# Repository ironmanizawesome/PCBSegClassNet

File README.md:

# PCB 회로도 복원 (Monorepo)

PCB 기판 사진으로부터 회로도(netlist)를 복원하는 프로젝트.
전체 목표·트랙 구조는 [project_outline.md](project_outline.md) 참조.

## 구조

```
.
├── component_seg/    Track B 1단계: 부품 검출/세그멘테이션 (TF, PCBSegClassNet 기반)
├── trace_seg/        Track B 3단계: 배선(trace) 세그멘테이션 (PyTorch, 자체 개발)
├── project_outline.md  프로젝트 전체 outline (Track A/B/C)
└── README.md
```

각 sub-project는 자체적인 `README.md`, `CLAUDE.md`, `requirements.txt`를
가짐. 두 프로젝트는 의존성·기술 스택이 분리됨 (TF vs PyTorch) — 한쪽에서
작업할 때는 해당 폴더로 `cd` 후 진행.

## 빠른 시작

```bash
# 부품 검출 작업
cd component_seg
# (component_seg/README.md 참조)

# 배선 검출 작업
cd trace_seg
# (trace_seg/README.md 참조)
```

## History

- `component_seg/`: 원래 [CandleLabAI/PCBSegClassNet](https://github.com/CandleLabAI/PCBSegClassNet) fork에서 출발, Arduino transfer learning 작업 추가
- `trace_seg/`: 자체 개발 (subtree merge로 통합, history 보존)

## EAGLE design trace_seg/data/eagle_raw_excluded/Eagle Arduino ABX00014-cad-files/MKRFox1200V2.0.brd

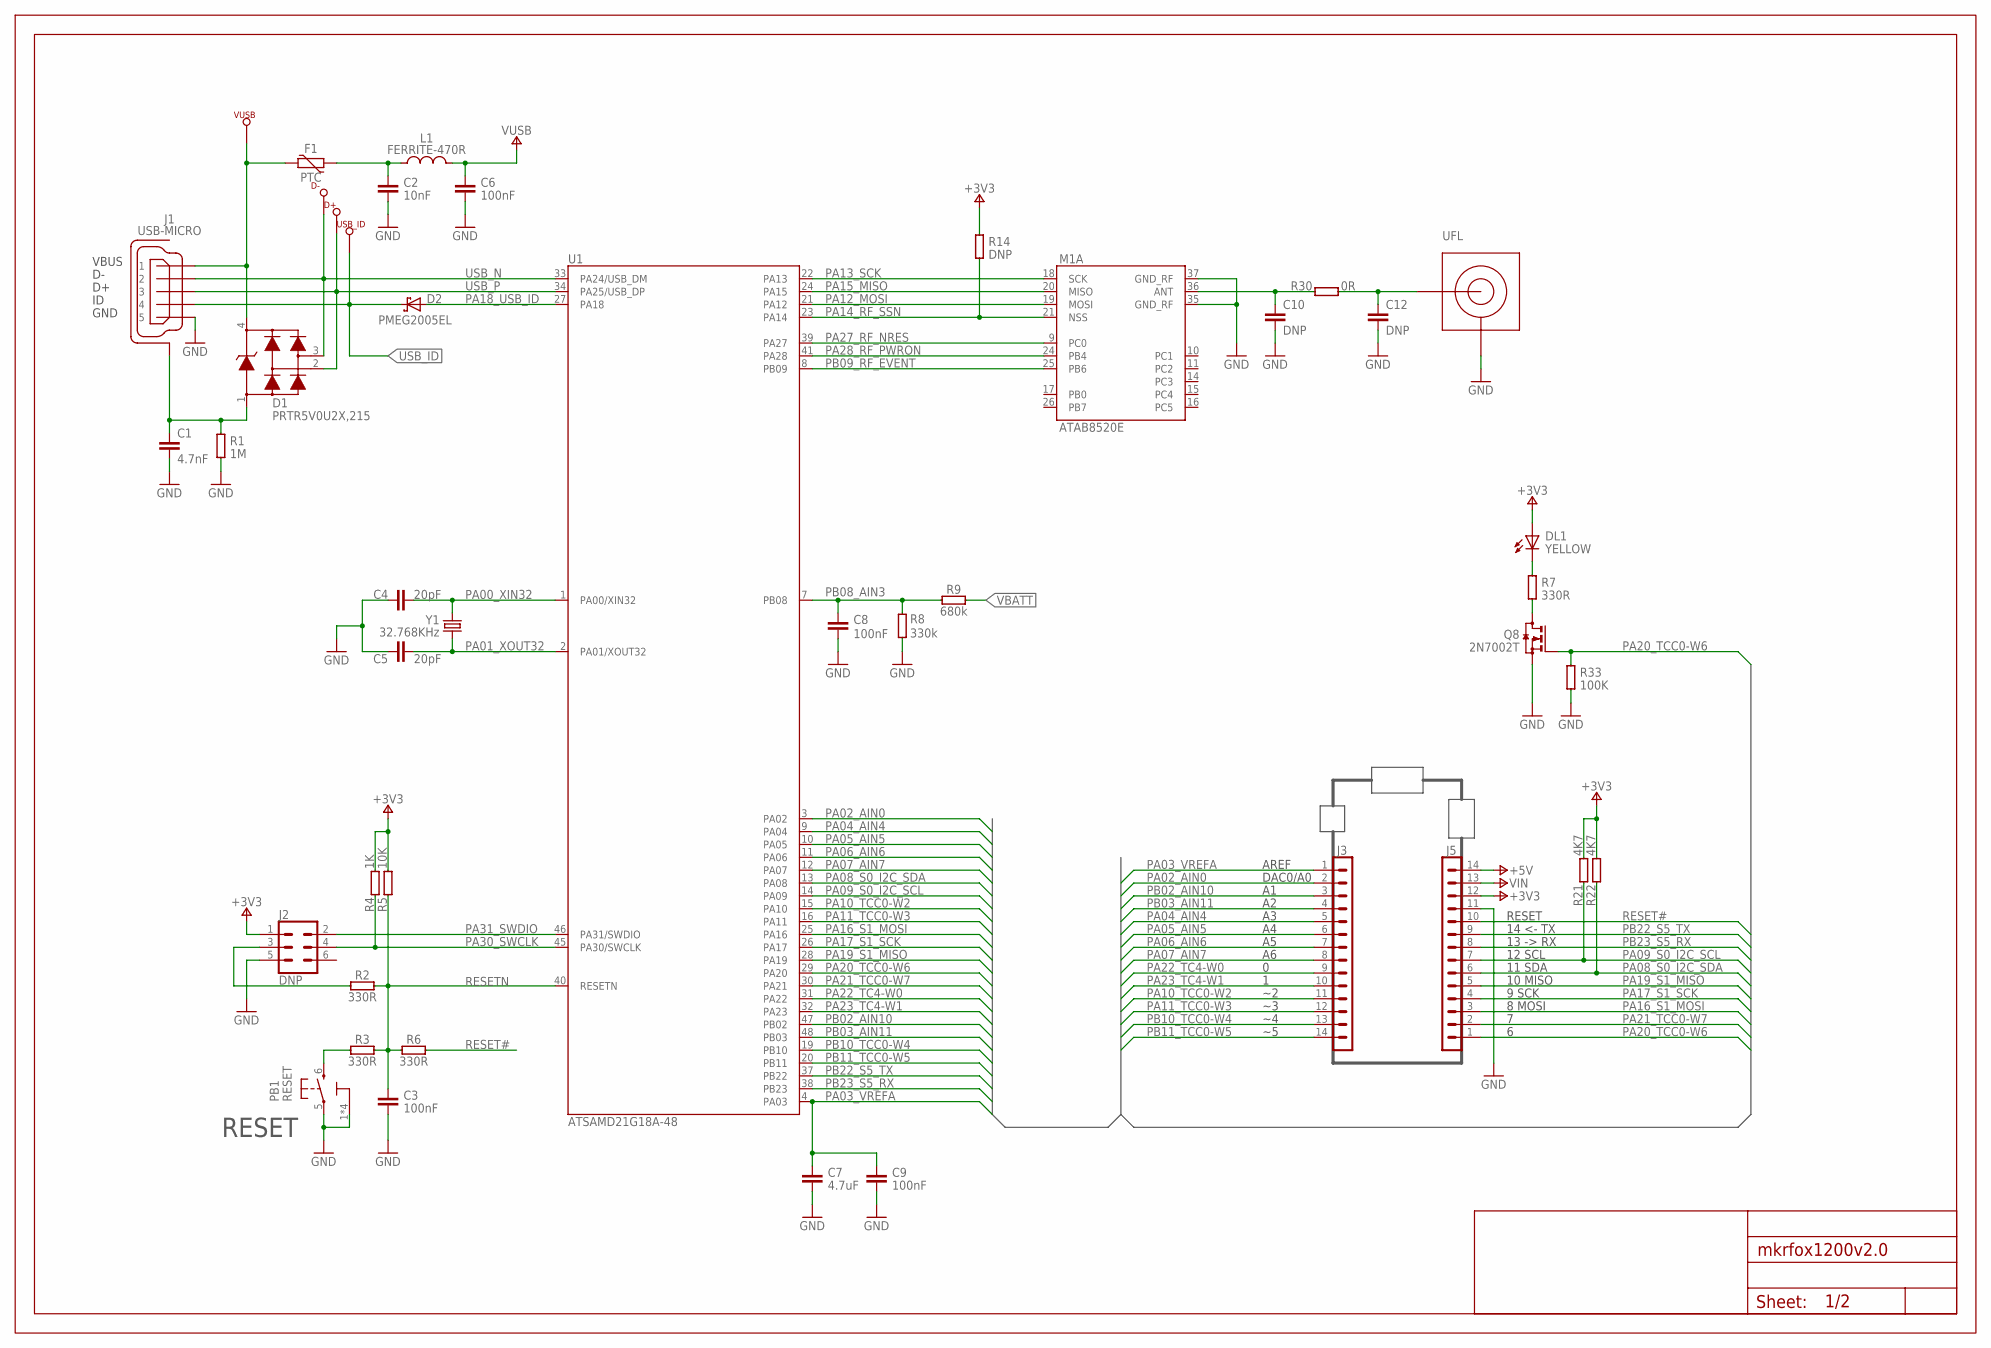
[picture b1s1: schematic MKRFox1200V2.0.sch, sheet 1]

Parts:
C1: 4.7nF; 0805-R2013X50N
C2: 10nF; 0402-1005X55N
C3, C6, C8, C9: 100nF; 0402-1005X55N
C4, C5: 20pF; 0402-1005X55N
C7: 4.7uF; 0402-1005X55N
C10, C12: DNP; 0402-1005X55N
D1: PRTR5V0U2X,215; SOT190P230X110-4N
D2: PMEG2005EL; SODFL1008X40N-882D
D+: TP1.00MM; TP-1.00MM
D-: TP1.00MM; TP-1.00MM
DL1: YELLOW; LEDC1608X80N-AK
F1: PTC; 0603-1608X90N
FRAME1: Page 1; FRAME
J1: USB-MICRO; ZX62-AB-5PA
J2: DNP; 2X3_SMT
J3, J5: DNP; 1X14_SMD_TH
J7: UFL; U.FL-R-SMT-1(60)
L1: FERRITE-470R; 0603-1608X90N@1
M1: ATAB8520E
PB1: RESET; C&K_PTS820_NO_HOLES
Q8: 2N7002T; SOTFL50P160X78-3
R1: 1M; 0402-1005X55N
R2, R3, R6, R7: 330R; 0402-1005X55N
R4: 1K; 0402-1005X55N
R5: 10K; 0402-1005X55N
R8: 330k; 0402-1005X55N
R9: 680k; 0402-1005X55N
R14: DNP; 0402-1005X55N
R21, R22: 4K7; 0402-1005X55N
R30: 0R; 0402-1005X55N
R33: 100K; 0402-1005X55N
U1: ATSAMD21G18A-48; QFN50P700X700X90-49XN-EPSQ515
USB_ID: TP1.00MM; TP-1.00MM
VUSB: TP1.00MM; TP-1.00MM
Y1: 32.768KHz; ABS07

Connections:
+3V3: DL1.A, J2.1, J5.12, R4.2, R5.2, R14.2, R21.2, R22.2; also elsewhere on the board
+5V: J5.14; also elsewhere on the board
GND: C1.2, C2.2, C3.2, C4.1, C5.1, C6.2, C7.2, C8.2, C9.2, C10.2, C12.2, J1.5, J2.5, J5.11, J7.GND1 (GND), J7.GND2 (GND), M1.35 (GND_RF), M1.37 (GND_RF), PB1.1 (3), PB1.2 (3), PB1.3, PB1.4 (3), PB1.5 (1), Q8.S, R1.1, R8.1, R33.1; also elsewhere on the board
N17650912: D1.4, F1.2, J1.1, VUSB.X
N17658775: PB1.6 (2), R3.1
unnamed: C1.1, D1.1, J1.6 (SH), J1.7 (SH), J1.8 (SH), J1.9 (SH), J1.10 (SH), J1.11 (SH), R1.2
unnamed: C2.1, F1.1, L1.1
unnamed: DL1.C, R7.2
unnamed: J2.3, R2.1
unnamed: Q8.D, R7.1
unnamed: C12.1, J7.SIG, R30.2
unnamed: C10.1, M1.36 (ANT), R30.1
PA00_XIN32: C4.2, U1.1 (PA00/XIN32), Y1.2
PA01_XOUT32: C5.2, U1.2 (PA01/XOUT32), Y1.1
PA02_AIN0: J3.2, U1.3 (PA02)
PA03_VREFA: C7.1, C9.1, J3.1, U1.4 (PA03)
PA04_AIN4: J3.5, U1.9 (PA04)
PA05_AIN5: J3.6, U1.10 (PA05)
PA06_AIN6: J3.7, U1.11 (PA06)
PA07_AIN7: J3.8, U1.12 (PA07)
PA08_S0_I2C_SDA: J5.6, R22.1, U1.13 (PA08)
PA09_S0_I2C_SCL: J5.7, R21.1, U1.14 (PA09)
PA10_TCC0-W2: J3.11, U1.15 (PA10)
PA11_TCC0-W3: J3.12, U1.16 (PA11)
PA12_MOSI: M1.19 (MOSI), U1.21 (PA12)
PA13_SCK: M1.18 (SCK), U1.22 (PA13)
PA14_RF_SSN: M1.21 (NSS), R14.1, U1.23 (PA14)
PA15_MISO: M1.20 (MISO), U1.24 (PA15)
PA16_S1_MOSI: J5.3, U1.25 (PA16)
PA17_S1_SCK: J5.4, U1.26 (PA17)
PA18_USB_ID: D2.A, U1.27 (PA18)
PA19_S1_MISO: J5.5, U1.28 (PA19)
PA20_TCC0-W6: J5.1, Q8.G, R33.2, U1.29 (PA20)
PA21_TCC0-W7: J5.2, U1.30 (PA21)
PA22_TC4-W0: J3.9, U1.31 (PA22)
PA23_TC4-W1: J3.10, U1.32 (PA23)
PA27_RF_NRES: M1.9 (PC0), U1.39 (PA27)
PA28_RF_PWRON: M1.24 (PB4), U1.41 (PA28)
PA30_SWCLK: J2.4, R4.1, U1.45 (PA30/SWCLK)
PA31_SWDIO: J2.2, U1.46 (PA31/SWDIO)
PB02_AIN10: J3.3, U1.47 (PB02)
PB03_AIN11: J3.4, U1.48 (PB03)
PB08_AIN3: C8.1, R8.2, R9.1, U1.7 (PB08)
PB09_RF_EVENT: M1.25 (PB6), U1.8 (PB09)
PB10_TCC0-W4: J3.13, U1.19 (PB10)
PB11_TCC0-W5: J3.14, U1.20 (PB11)
PB22_S5_TX: J5.9, U1.37 (PB22)
PB23_S5_RX: J5.8, U1.38 (PB23)
RESET#: J5.10, R6.2
RESETN: C3.1, R2.2, R3.2, R5.1, R6.1, U1.40 (RESETN)
USB_ID: D2.C, J1.4, USB_ID.X; also elsewhere on the board
USB_N: D1.3, D-.X, J1.2, U1.33 (PA24/USB_DM)
USB_P: D1.2, D+.X, J1.3, U1.34 (PA25/USB_DP)
VBATT: R9.2; also elsewhere on the board
VIN: J5.13; also elsewhere on the board
VUSB: C6.1, L1.2; also elsewhere on the board

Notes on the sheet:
14 <- TX
13 -> RX
12 SCL
RESET
11 SDA
8 MOSI
9 SCK
10 MISO
AREF
DAC0/A0

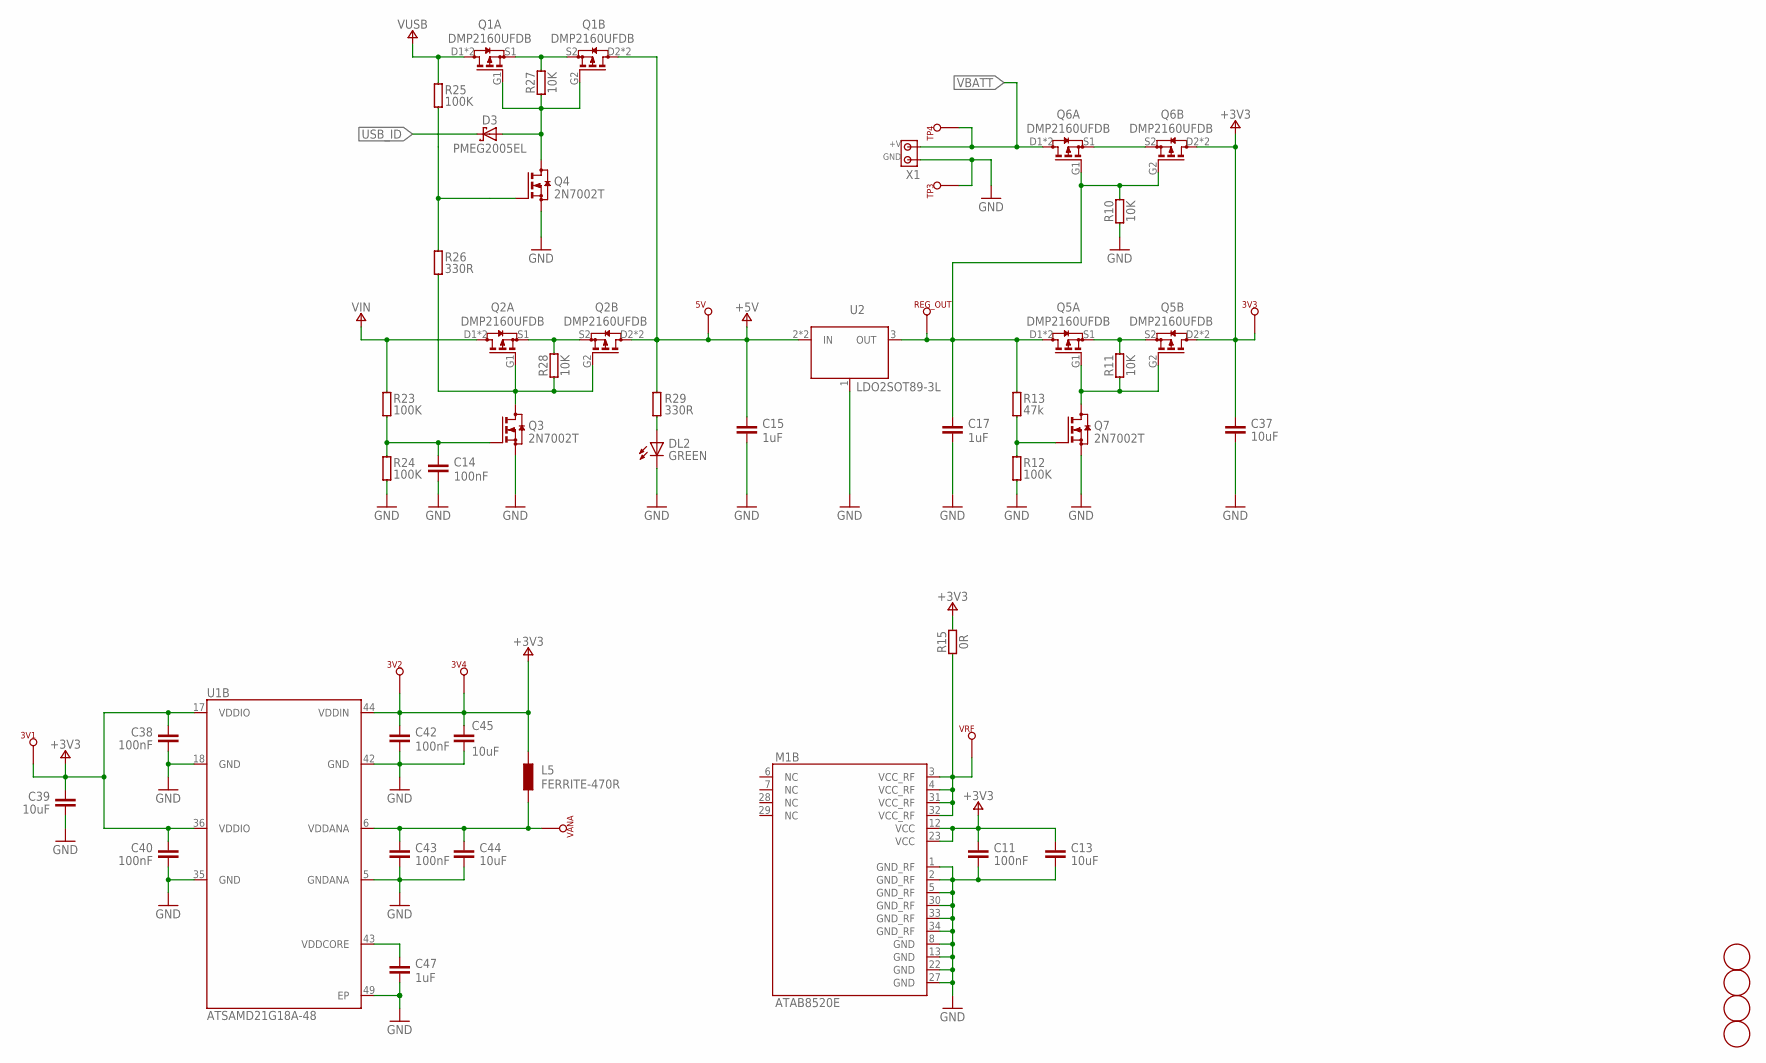
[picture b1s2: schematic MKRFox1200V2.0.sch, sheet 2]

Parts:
3V1, 3V2, 3V3, 3V4, 5V: TP0.5MM; TP-0.50MM
C11, C14, C38, C40, C42, C43: 100nF; 0402-1005X55N
C13, C37, C39, C44, C45: 10uF; 0603-1608X90N
C15, C17, C47: 1uF; 0402-1005X55N
D3: PMEG2005EL; SODFL1008X40N-882D
DL2: GREEN; LEDC1608X80N-AK
FD1, FD2, FD3, FD4: FIDUCIAL-1.5MM; FD-1-1.5
L5: FERRITE-470R; 0603-1608X90N@1
M1: ATAB8520E
Q1, Q2, Q5, Q6: DMP2160UFDB; PWR_SC70
Q3, Q4, Q7: 2N7002T; SOTFL50P160X78-3
R10, R11, R27, R28: 10K; 0402-1005X55N
R12, R23, R24, R25: 100K; 0402-1005X55N
R13: 47k; 0402-1005X55N
R15: 0R; 0402-1005X55N
R26, R29: 330R; 0402-1005X55N
REG_OUT: TP0.5MM; TP-0.50MM
TP3, TP4: TP1.00MM; TP-1.00MM
U1: ATSAMD21G18A-48; QFN50P700X700X90-49XN-EPSQ515
U2: LDO2SOT89-3L; SOT89-3L
VANA: TP0.5MM; TP-0.50MM
VRF: TP0.5MM; TP-0.50MM
X1: SCREW2X2.54; SCREW2

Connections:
+3V3: 3V1.X, 3V2.X, 3V3.X, 3V4.X, C11.1, C13.1, C37.1, C38.1, C39.1, C40.1, C42.1, C45.1, L5.1, M1.12 (VCC), M1.23 (VCC), Q5.D2 (D), Q5.D2' (D), Q6.D2 (D), Q6.D2' (D), R15.2, U1.17 (VDDIO), U1.36 (VDDIO), U1.44 (VDDIN); also elsewhere on the board
+5V: 5V.X, C15.1, Q1.D2 (D), Q1.D2' (D), Q2.D2 (D), Q2.D2' (D), R29.2, U2.2 (IN), U2.TH (IN); also elsewhere on the board
GND: C11.2, C13.2, C14.2, C15.2, C17.2, C37.2, C38.2, C39.2, C40.2, C42.2, C43.2, C44.2, C45.2, C47.2, DL2.C, M1.1 (GND_RF), M1.2 (GND_RF), M1.5 (GND_RF), M1.8 (GND), M1.13 (GND), M1.22 (GND), M1.27 (GND), M1.30 (GND_RF), M1.33 (GND_RF), M1.34 (GND_RF), Q3.S, Q4.S, Q7.S, R10.1, R12.1, R24.1, TP3.X, U1.5 (GNDANA), U1.18 (GND), U1.35 (GND), U1.42 (GND), U1.49 (EP), U2.1 (GND/ADJ), X1.GND; also elsewhere on the board
N1: Q5.S1 (S), Q5.S2 (S), R11.2
N2: Q5.G1 (G), Q5.G2 (G), Q7.D, R11.1
N3: Q7.G, R12.2, R13.1
N17690335: Q1.S1 (S), Q1.S2 (S), R27.2
N17690346: D3.A, Q1.G1 (G), Q1.G2 (G), Q4.D, R27.1
N17690381: Q4.G, R25.1, R26.2
N17690821: Q2.S1 (S), Q2.S2 (S), R28.2
N17690840: Q2.G1 (G), Q2.G2 (G), Q3.D, R26.1, R28.1
N17690878: C14.1, Q3.G, R23.1, R24.2
N17834267: DL2.A, R29.1
N17852357: C43.1, C44.1, L5.2, U1.6 (VDDANA), VANA.X
unnamed: M1.3 (VCC_RF), M1.4 (VCC_RF), M1.31 (VCC_RF), M1.32 (VCC_RF), R15.1, VRF.X
unnamed: C17.1, Q5.D1 (D), Q5.D1' (D), Q6.G1 (G), Q6.G2 (G), R10.2, R13.2, REG_OUT.X, U2.3 (OUT)
unnamed: Q6.S1 (S), Q6.S2 (S)
unnamed: C47.1, U1.43 (VDDCORE)
USB_ID: D3.C; also elsewhere on the board
VBATT: Q6.D1 (D), Q6.D1' (D), TP4.X, X1.V+; also elsewhere on the board
VIN: Q2.D1 (D), Q2.D1' (D), R23.2; also elsewhere on the board
VUSB: Q1.D1 (D), Q1.D1' (D), R25.2; also elsewhere on the board

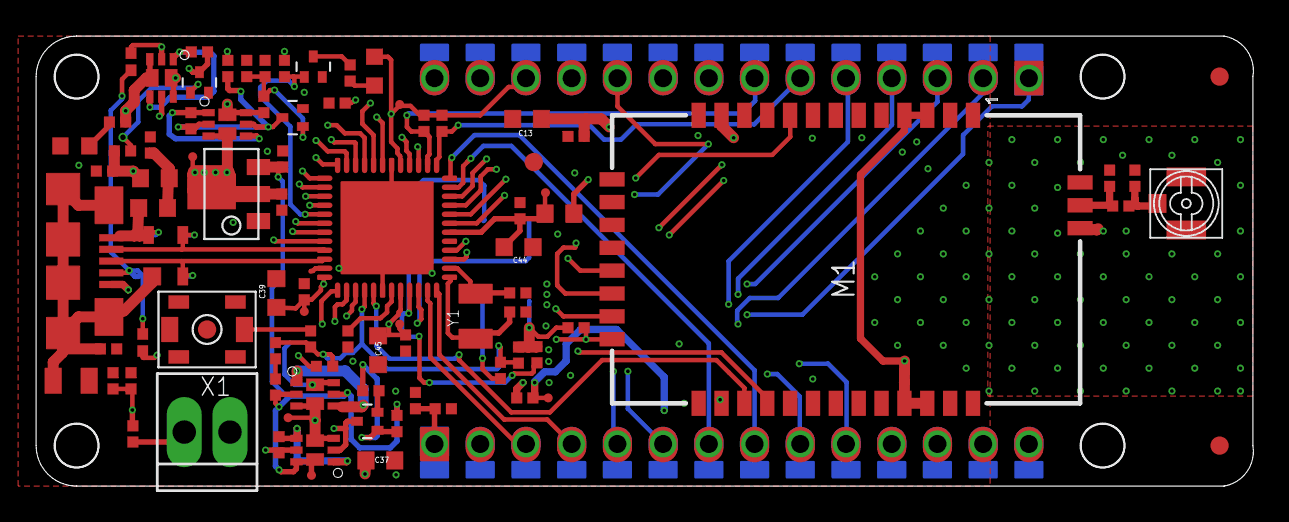
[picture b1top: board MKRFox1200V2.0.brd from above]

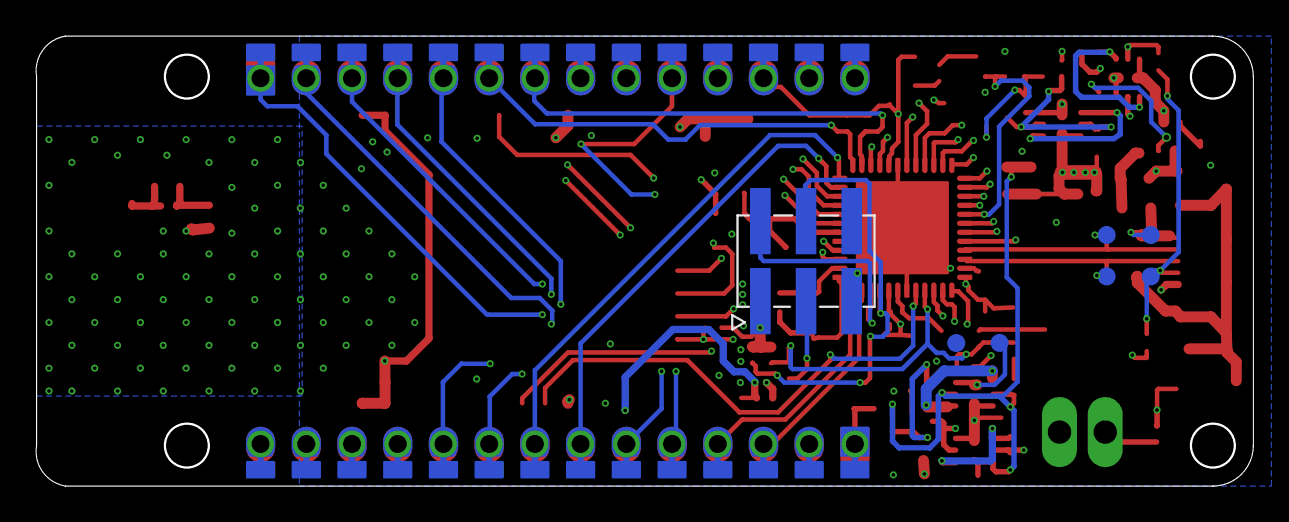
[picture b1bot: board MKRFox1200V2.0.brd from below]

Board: 4 copper layers, 67.6 x 25.0 mm, 101 parts (9 on the bottom side), 71 nets.

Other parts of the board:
U$5, U$6, U$7, U$8: MH_RND_F_2.2MM_NM

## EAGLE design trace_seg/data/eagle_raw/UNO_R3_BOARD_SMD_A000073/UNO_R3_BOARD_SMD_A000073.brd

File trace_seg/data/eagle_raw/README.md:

# Eagle / Gerber 파일 디렉토리

## Arduino Leonardo Gerber 파일 확보 방법

Arduino Leonardo는 오픈소스 하드웨어다. 공식 설계 파일은 아래 경로에서 받을 수 있다.

### GitHub에서 직접 다운로드

1. https://github.com/arduino/ArduinoCore-avr 접속
2. `variants/leonardo/` 디렉토리 → Eagle `.brd` 파일 확인
3. 또는 릴리즈 페이지에서 `ArduinoCore-avr-x.x.x.zip` 다운로드

### Gerber 파일이 이미 있는 경우

Arduino 공식 리포지토리 일부 릴리즈는 `/extras/` 하위에 Gerber 파일을 포함한다.

### Eagle .brd → Gerber 변환 (직접 생성)

1. Eagle CAD (무료 버전 가능) 또는 KiCad에서 `.brd` 파일 열기
2. File → CAM Processor → `gerb274x.cam` 실행
3. 출력 파일:
   - `*.GTL` — Top Copper Layer    ← 앞면 배선 GT
   - `*.GBL` — Bottom Copper Layer ← 뒷면 배선 GT
   - `*.GBO` — Board Outline

### 이 디렉토리에 놓을 파일

```
eagle/
├── README.md            ← 이 파일
├── Leonardo.brd         ← Eagle 보드 파일 (옵션)
├── Leonardo.sch         ← Eagle 회로도 파일 (옵션)
└── gerber/
    ├── Leonardo.GTL     ← 앞면 구리 레이어 Gerber
    ├── Leonardo.GBL     ← 뒷면 구리 레이어 Gerber
    └── Leonardo.GBO     ← 보드 외곽선
```

## GT 마스크 생성 실행 방법

Gerber 파일을 위 경로에 배치한 후:

```bash
# 앞면 GT 마스크 생성
python src/segmentation/gerber_to_mask.py \
    --input eagle/gerber/Leonardo.GTL \
    --output data/masks/gt_front.png \
    --dpi 500

# 뒷면 GT 마스크 생성 (좌우 반전 적용)
python src/segmentation/gerber_to_mask.py \
    --input eagle/gerber/Leonardo.GBL \
    --output data/masks/gt_back.png \
    --dpi 500 --flip-horizontal

# PCB 사진 크기에 맞춰 리사이즈 (1000x750 사진 기준)
python src/segmentation/gerber_to_mask.py \
    --input eagle/gerber/Leonardo.GTL \
    --output data/masks/gt_front.png \
    --dpi 500 --target-width 1000 --target-height 750
```

## 주의사항

- Gerber → 사진 정합(image registration)은 별도 작업 필요
  - DPI 기반 단순 리사이즈: 보드 크기가 동일하면 근사 가능
  - 정확한 정합: 패드 위치 기준 homography 변환 사용
- Arduino Leonardo 보드 크기: 약 68.6mm × 53.4mm

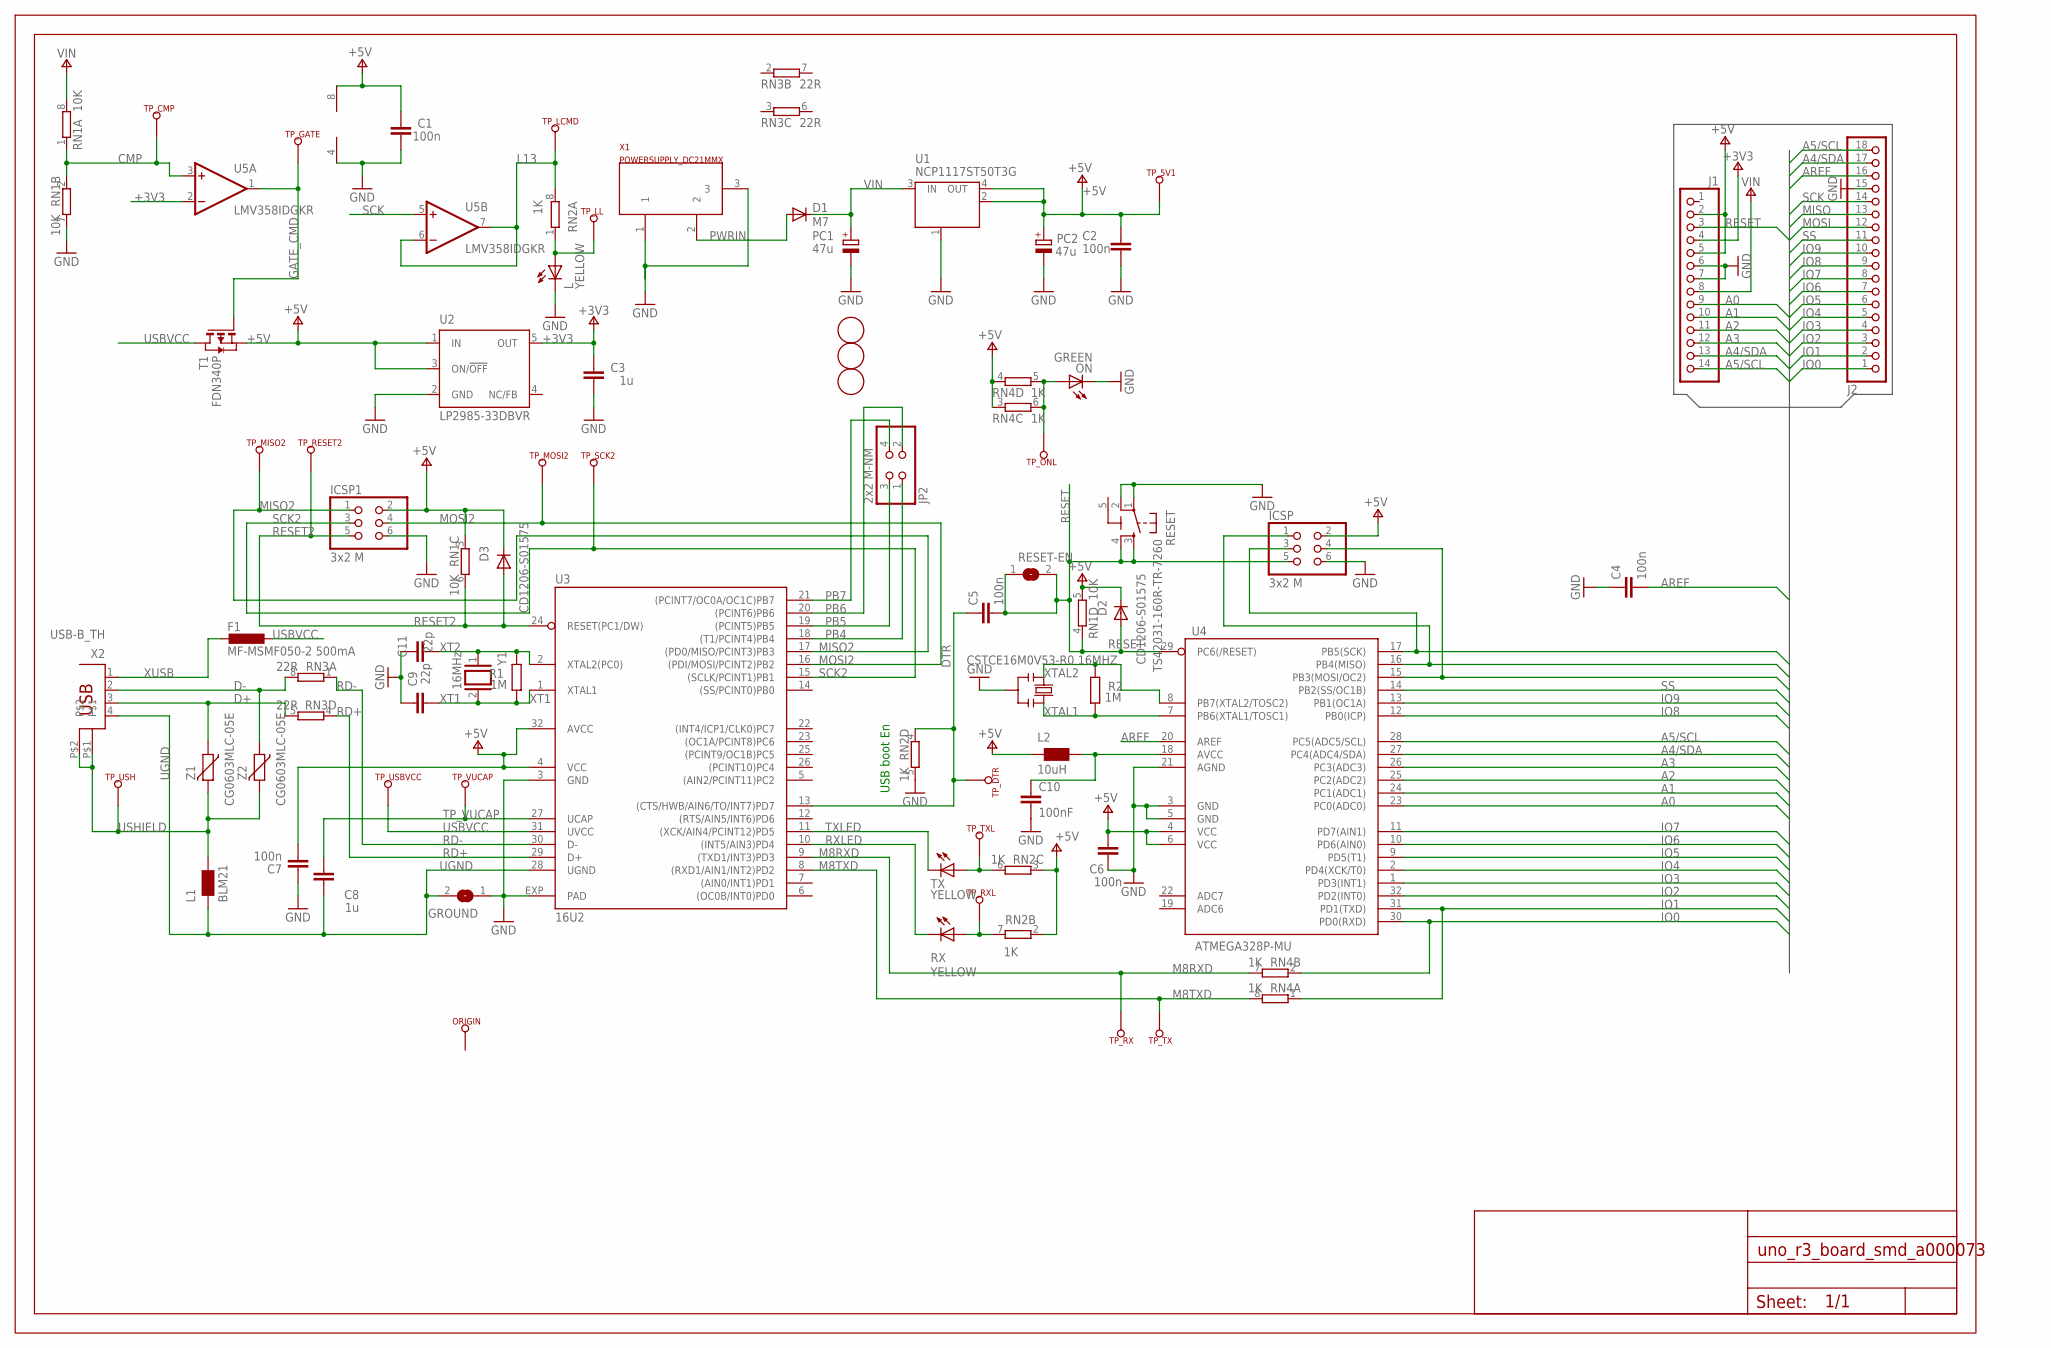
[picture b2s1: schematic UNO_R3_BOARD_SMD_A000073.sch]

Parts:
C1, C2, C4, C5, C6, C7: 100n; C0603-ROUND
C3, C8: 1u; C0603-ROUND
C9, C11: 22p; C0603-ROUND
C10: 100nF; C0603-ROUND
D1: M7; SMB
D2, D3: CD1206-S01575; MINIMELF
F1: MF-MSMF050-2 500mA; L1812
FD1, FD2, FD3: DNP; FD-1-1.5
FRAME1: DNP; FRAME
GROUND: SJ
ICSP, ICSP1: 3x2 M; 2X03
J1: -; 1X14-CUSTOM
J2: -; 1X18-CUSTOM
JP2: 2x2 M-NM; 2X02
L: YELLOW; CHIP-LED0805
L1: BLM21; 0805
L2: 10uH; 0805
ON: GREEN; CHIP-LED0805
ORIGIN: TP_SP; TP-SP
PC1, PC2: 47u; PANASONIC_D
R1, R2: 1M; R0603-ROUND
RESET: TS42031-160R-TR-7260; TS42
RESET-EN: SJ
RN1: 10K; CAY16
RN2, RN4: 1K; CAY16
RN3: 22R; CAY16
RX: YELLOW; CHIP-LED0805
T1: FDN340P; SOT-23
TP_5V1: TP_SP; TP-SP
TP_CMP: TP_SP; TP-SP
TP_DTR: TP_SP; TP-SP
TP_GATE: TP_SP; TP-SP
TP_LCMD: TP_SP; TP-SP
TP_LL: TP_SP; TP-SP
TP_MISO2: TP_SP; TP-SP
TP_MOSI2: TP_SP; TP-SP
TP_ONL: TP_SP; TP-SP
TP_RESET2: TP_SP; TP-SP
TP_RX: TP_SP; TP-SP
TP_RXL: TP_SP; TP-SP
TP_SCK2: TP_SP; TP-SP
TP_TX: TP_SP; TP-SP
TP_TXL: TP_SP; TP-SP
TP_USBVCC: TP_SP; TP-SP
TP_USH: TP_SP; TP-SP
TP_VUCAP: TP_SP; TP-SP
TX: YELLOW; CHIP-LED0805
U1: NCP1117ST50T3G; SOT223
U2: LP2985-33DBVR; SOT23-DBV
U3: 16U2; ATMEL_QFN32
U4: ATMEGA328P-MU; MLF32
U5: LMV358IDGKR; MSOP08
X1: POWERSUPPLY_DC21MMX; POWERSUPPLY_DC-21MM
X2: USB-B_TH; PN61729
Y1: 16MHz; QS
Y2: CSTCE16M0V53-R0 16MHZ; RESONATOR
Z1, Z2: CG0603MLC-05E; CT/CN0603

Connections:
5-GND: RESET.5 (5-GND)
+3V3: C3.2, J1.4, U2.5 (OUT), U5.2 (-IN)
+5V: C1.2, C2.2, C6.2, C7.1, D2.C, D3.C, ICSP.2, ICSP1.2, J1.2, J1.5, L2.1, PC2.+, RN1.3 (1), RN1.5 (2), RN2.2 (1), RN2.3 (1), RN4.3 (1), RN4.4 (1), T1.2 (S), TP_5V1.X, U1.2 (OUT), U1.4 (OUT), U2.1 (IN), U2.3 (ON/!OFF), U3.4 (VCC), U3.32 (AVCC), U4.4 (VCC), U4.6 (VCC), U5.8 (V+)
A0: J1.9, U4.23 (PC0(ADC0))
A1: J1.10, U4.24 (PC1(ADC1))
A2: J1.11, U4.25 (PC2(ADC2))
A3: J1.12, U4.26 (PC3(ADC3))
A4/SDA: J1.13, J2.17, U4.27 (PC4(ADC4/SDA))
A5/SCL: J1.14, J2.18, U4.28 (PC5(ADC5/SCL))
AREF: C4.2, J2.16, U4.20 (AREF)
CMP: RN1.1, RN1.2 (1), TP_CMP.X, U5.3 (+IN)
D+: RN3.5 (2), X2.3, Z1.1
D-: RN3.8 (2), X2.2, Z2.1
DTR: C5.1, RN2.4 (1), TP_DTR.X, U3.13 ((CTS/HWB/AIN6/TO/INT7)PD7)
GATE_CMD: T1.3 (G), TP_GATE.X, U5.1 (OUT)
GND: C1.1, C2.1, C3.1, C4.1, C6.1, C7.2, C9.2, C10.2, C11.2, GROUND.1, ICSP.6, ICSP1.6, J1.6, J1.7, J2.15, L.C, ON.C, PC1.-, PC2.-, RESET.1, RESET.2, RN1.7 (2), RN2.5 (2), U1.1 (GND/ADJ), U2.2 (GND), U3.3 (GND), U3.EXP (PAD), U4.3 (GND), U4.5 (GND), U4.21 (AGND), U5.4 (V-), X1.1, X1.3, Y2.2
IO0: J2.1, RN4.2 (1), U4.30 (PD0(RXD))
IO1: J2.2, RN4.1, U4.31 (PD1(TXD))
IO2: J2.3, U4.32 (PD2(INT0))
IO3: J2.4, U4.1 (PD3(INT1))
IO4: J2.5, U4.2 (PD4(XCK/T0))
IO5: J2.6, U4.9 (PD5(T1))
IO6: J2.7, U4.10 (PD6(AIN0))
IO7: J2.8, U4.11 (PD7(AIN1))
IO8: J2.9, U4.12 (PB0(ICP))
IO9: J2.10, U4.13 (PB1(OC1A))
L13: RN2.8 (2), TP_LCMD.X, U5.6 (-IN), U5.7 (OUT)
M8RXD: RN4.7 (2), TP_RX.X, U3.9 ((TXD1/INT3)PD3)
M8TXD: RN4.8 (2), TP_TX.X, U3.8 ((RXD1/AIN1/INT2)PD2)
MISO: ICSP.1, J2.13, U4.16 (PB4(MISO))
MISO2: ICSP1.1, TP_MISO2.X, U3.17 ((PD0/MISO/PCINT3)PB3)
MOSI: ICSP.4, J2.12, U4.15 (PB3(MOSI/OC2))
MOSI2: ICSP1.4, TP_MOSI2.X, U3.16 ((PDI/MOSI/PCINT2)PB2)
unnamed: L.A, RN2.1, TP_LL.X
unnamed: ON.A, RN4.5 (2), RN4.6 (2), TP_ONL.X
unnamed: C10.1, L2.2, U4.18 (AVCC)
unnamed: RN2.7 (2), RX.A, TP_RXL.X
unnamed: RN2.6 (2), TP_TXL.X, TX.A
PB4: JP2.1, U3.18 ((T1/PCINT4)PB4)
PB5: JP2.3, U3.19 ((PCINT5)PB5)
PB6: JP2.2, U3.20 ((PCINT6)PB6)
PB7: JP2.4, U3.21 ((PCINT7/OC0A/OC1C)PB7)
PWRIN: D1.A, X1.2
RD+: RN3.4 (1), U3.29 (D+)
RD-: RN3.1, U3.30 (D-)
RESET: C5.2, D2.A, ICSP.5, J1.3, RESET.3, RESET.4, RESET-EN.1, RESET-EN.2, RN1.4 (1), U4.29 (PC6(/RESET))
RESET2: D3.A, ICSP1.5, RN1.6 (2), TP_RESET2.X, U3.24 (RESET(PC1/DW))
RXLED: RX.C, U3.10 ((INT5/AIN3)PD4)
SCK: ICSP.3, J2.14, U4.17 (PB5(SCK)), U5.5 (+IN)
SCK2: ICSP1.3, TP_SCK2.X, U3.15 ((SCLK/PCINT1)PB1)
SS: J2.11, U4.14 (PB2(SS/OC1B))
TP_VUCAP: C8.1, TP_VUCAP.X, U3.27 (UCAP)
TXLED: TX.C, U3.11 ((XCK/AIN4/PCINT12)PD5)
UGND: C8.2, GROUND.2, L1.1, U3.28 (UGND), X2.4
USBVCC: F1.1, T1.1 (D), TP_USBVCC.X, U3.31 (UVCC)
USHIELD: L1.2, TP_USH.X, X2.P$1, X2.P$2, Z1.2, Z2.2
VIN: D1.C, J1.8, PC1.+, RN1.8 (2), U1.3 (IN)
XT1: C9.1, R1.1, U3.1 (XTAL1), Y1.2
XT2: C11.1, R1.2, U3.2 (XTAL2(PC0)), Y1.1
XTAL1: R2.1, U4.7 (PB6(XTAL1/TOSC1)), Y2.3
XTAL2: R2.2, U4.8 (PB7(XTAL2/TOSC2)), Y2.1
XUSB: F1.2, X2.1

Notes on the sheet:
USB boot En

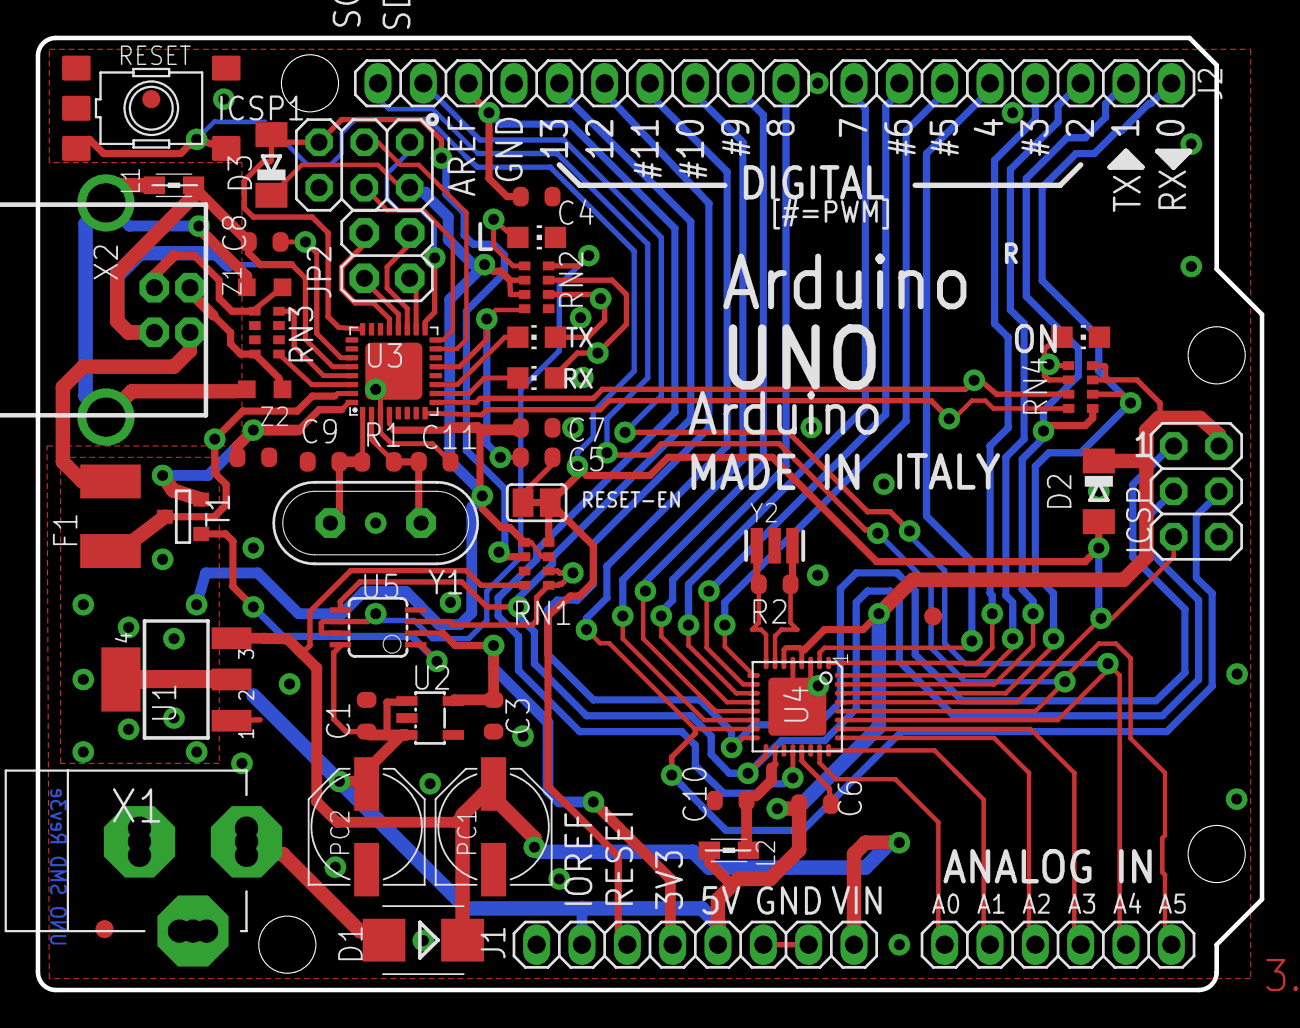
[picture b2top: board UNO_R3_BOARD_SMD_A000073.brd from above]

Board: 2 copper layers, 68.6 x 53.3 mm, 72 parts (1 on the bottom side), 61 nets.

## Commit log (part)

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2026-04-02 Initialize README with project details and stages
    Added project overview and stages for PCB wiring segmentation.
2026-05-11 Colab을 통해 생성됨
2026-05-25 Add dangerous-check and format hooks
    Introduce .claude/hooks/check_dangerous.py to detect and block dangerous shell patterns (e.g. rm -rf variants, fork bombs, mkfs, dd, piping to sh/bash) and prevent rm -rf on protected directories, an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

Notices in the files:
parts and their libraries:
Arduino-utility: Copyright (c) 2016-2017 Arduino LLC.  All right reserved.
Arduino-utility: This file is licensed under : CC-SA-BY-NC
